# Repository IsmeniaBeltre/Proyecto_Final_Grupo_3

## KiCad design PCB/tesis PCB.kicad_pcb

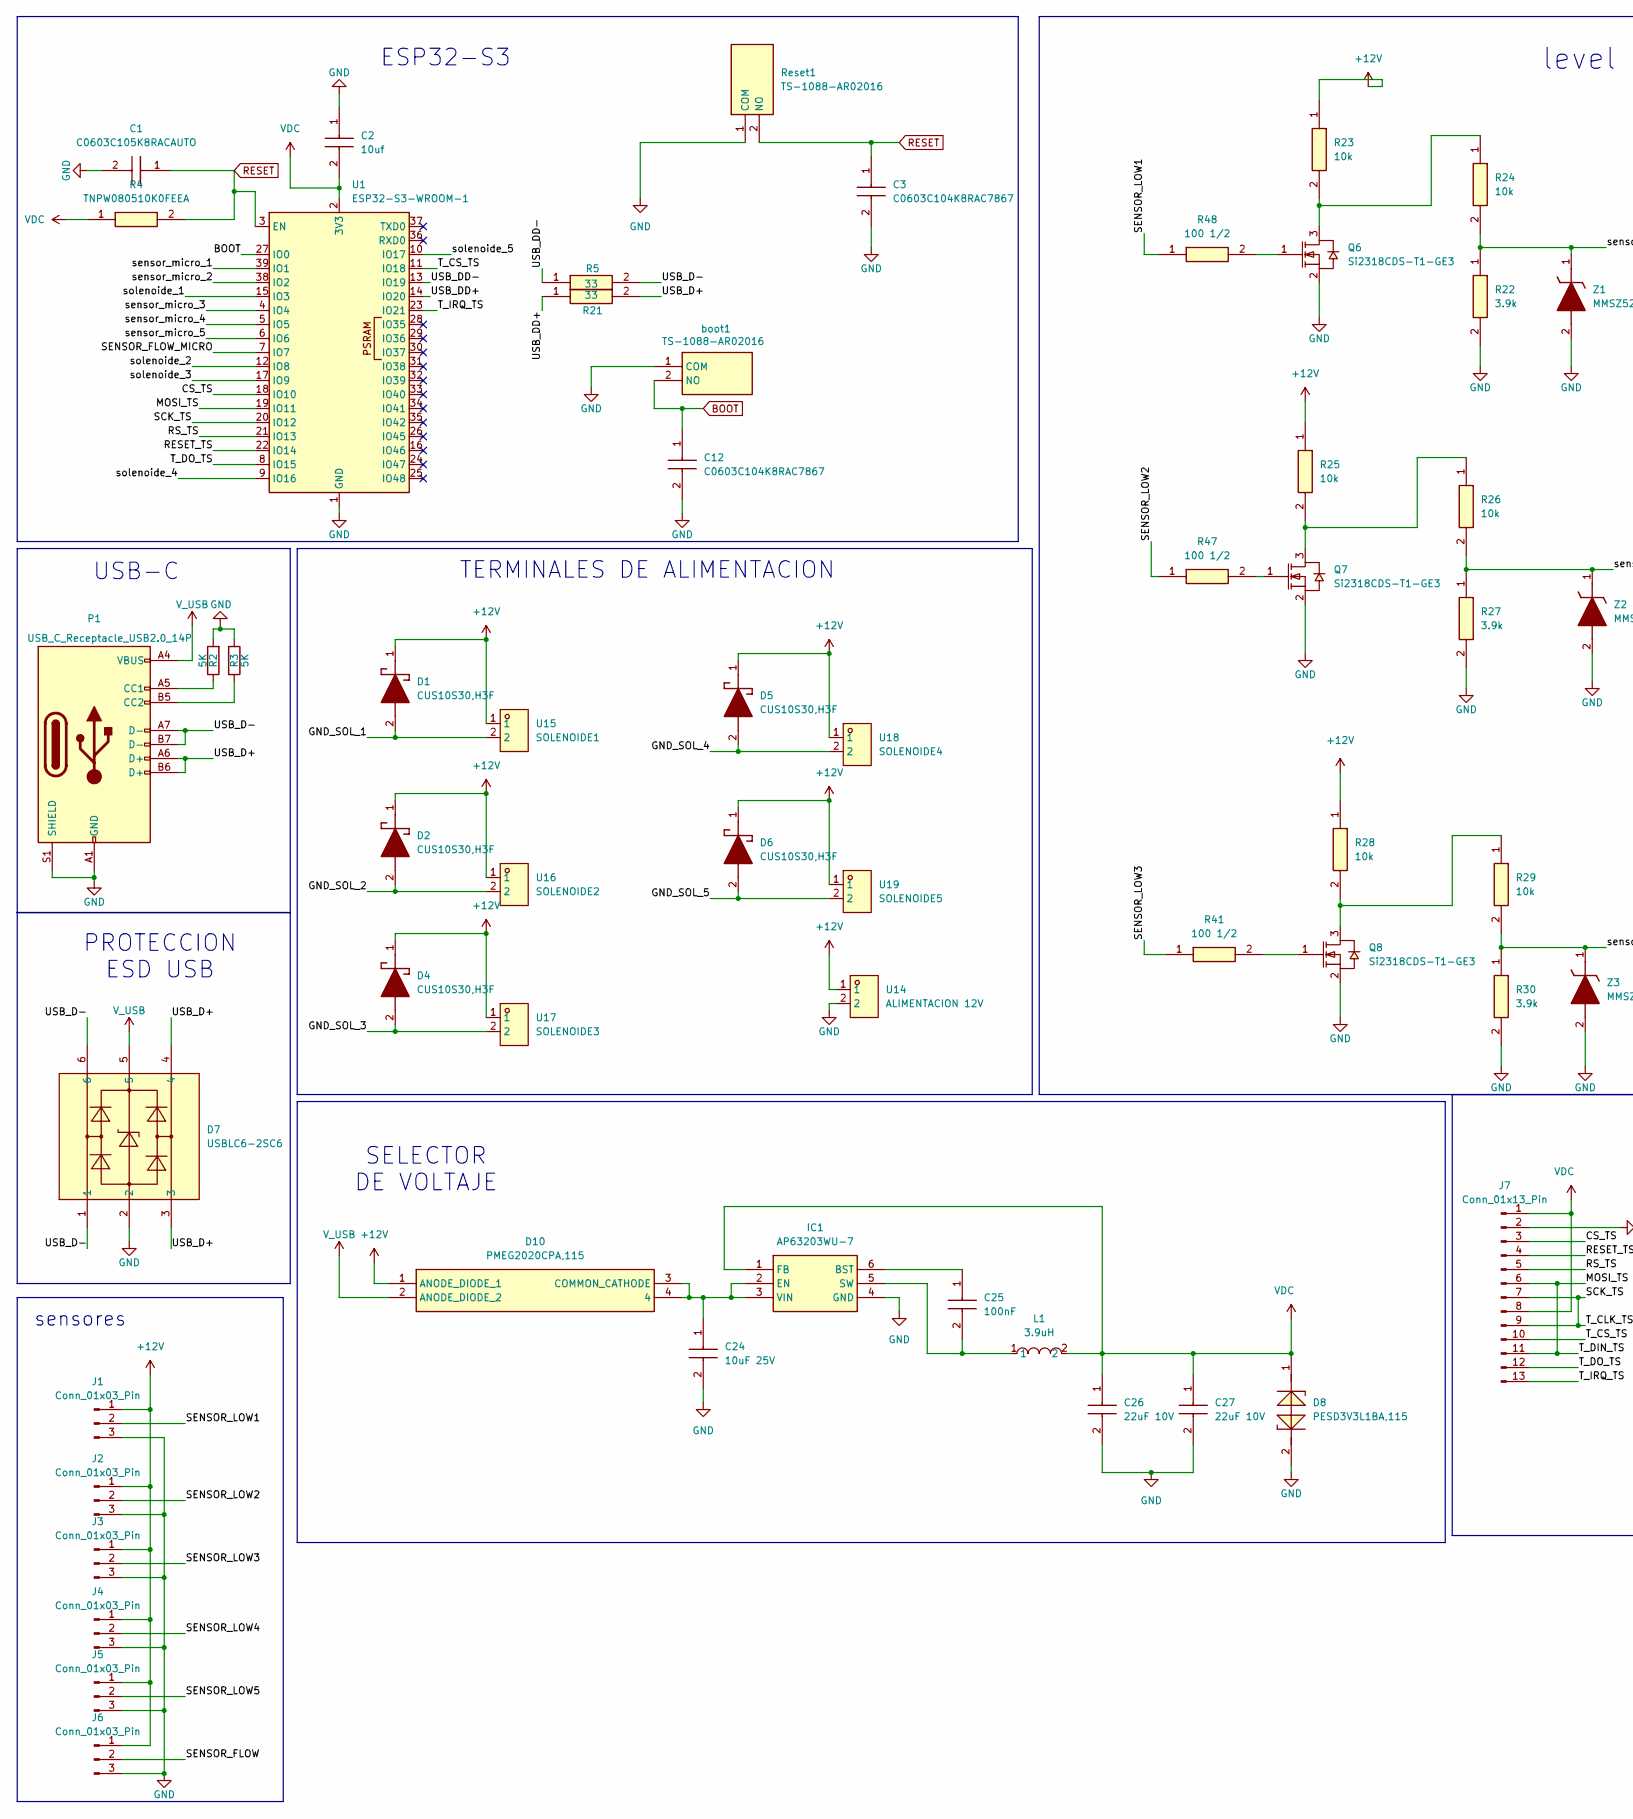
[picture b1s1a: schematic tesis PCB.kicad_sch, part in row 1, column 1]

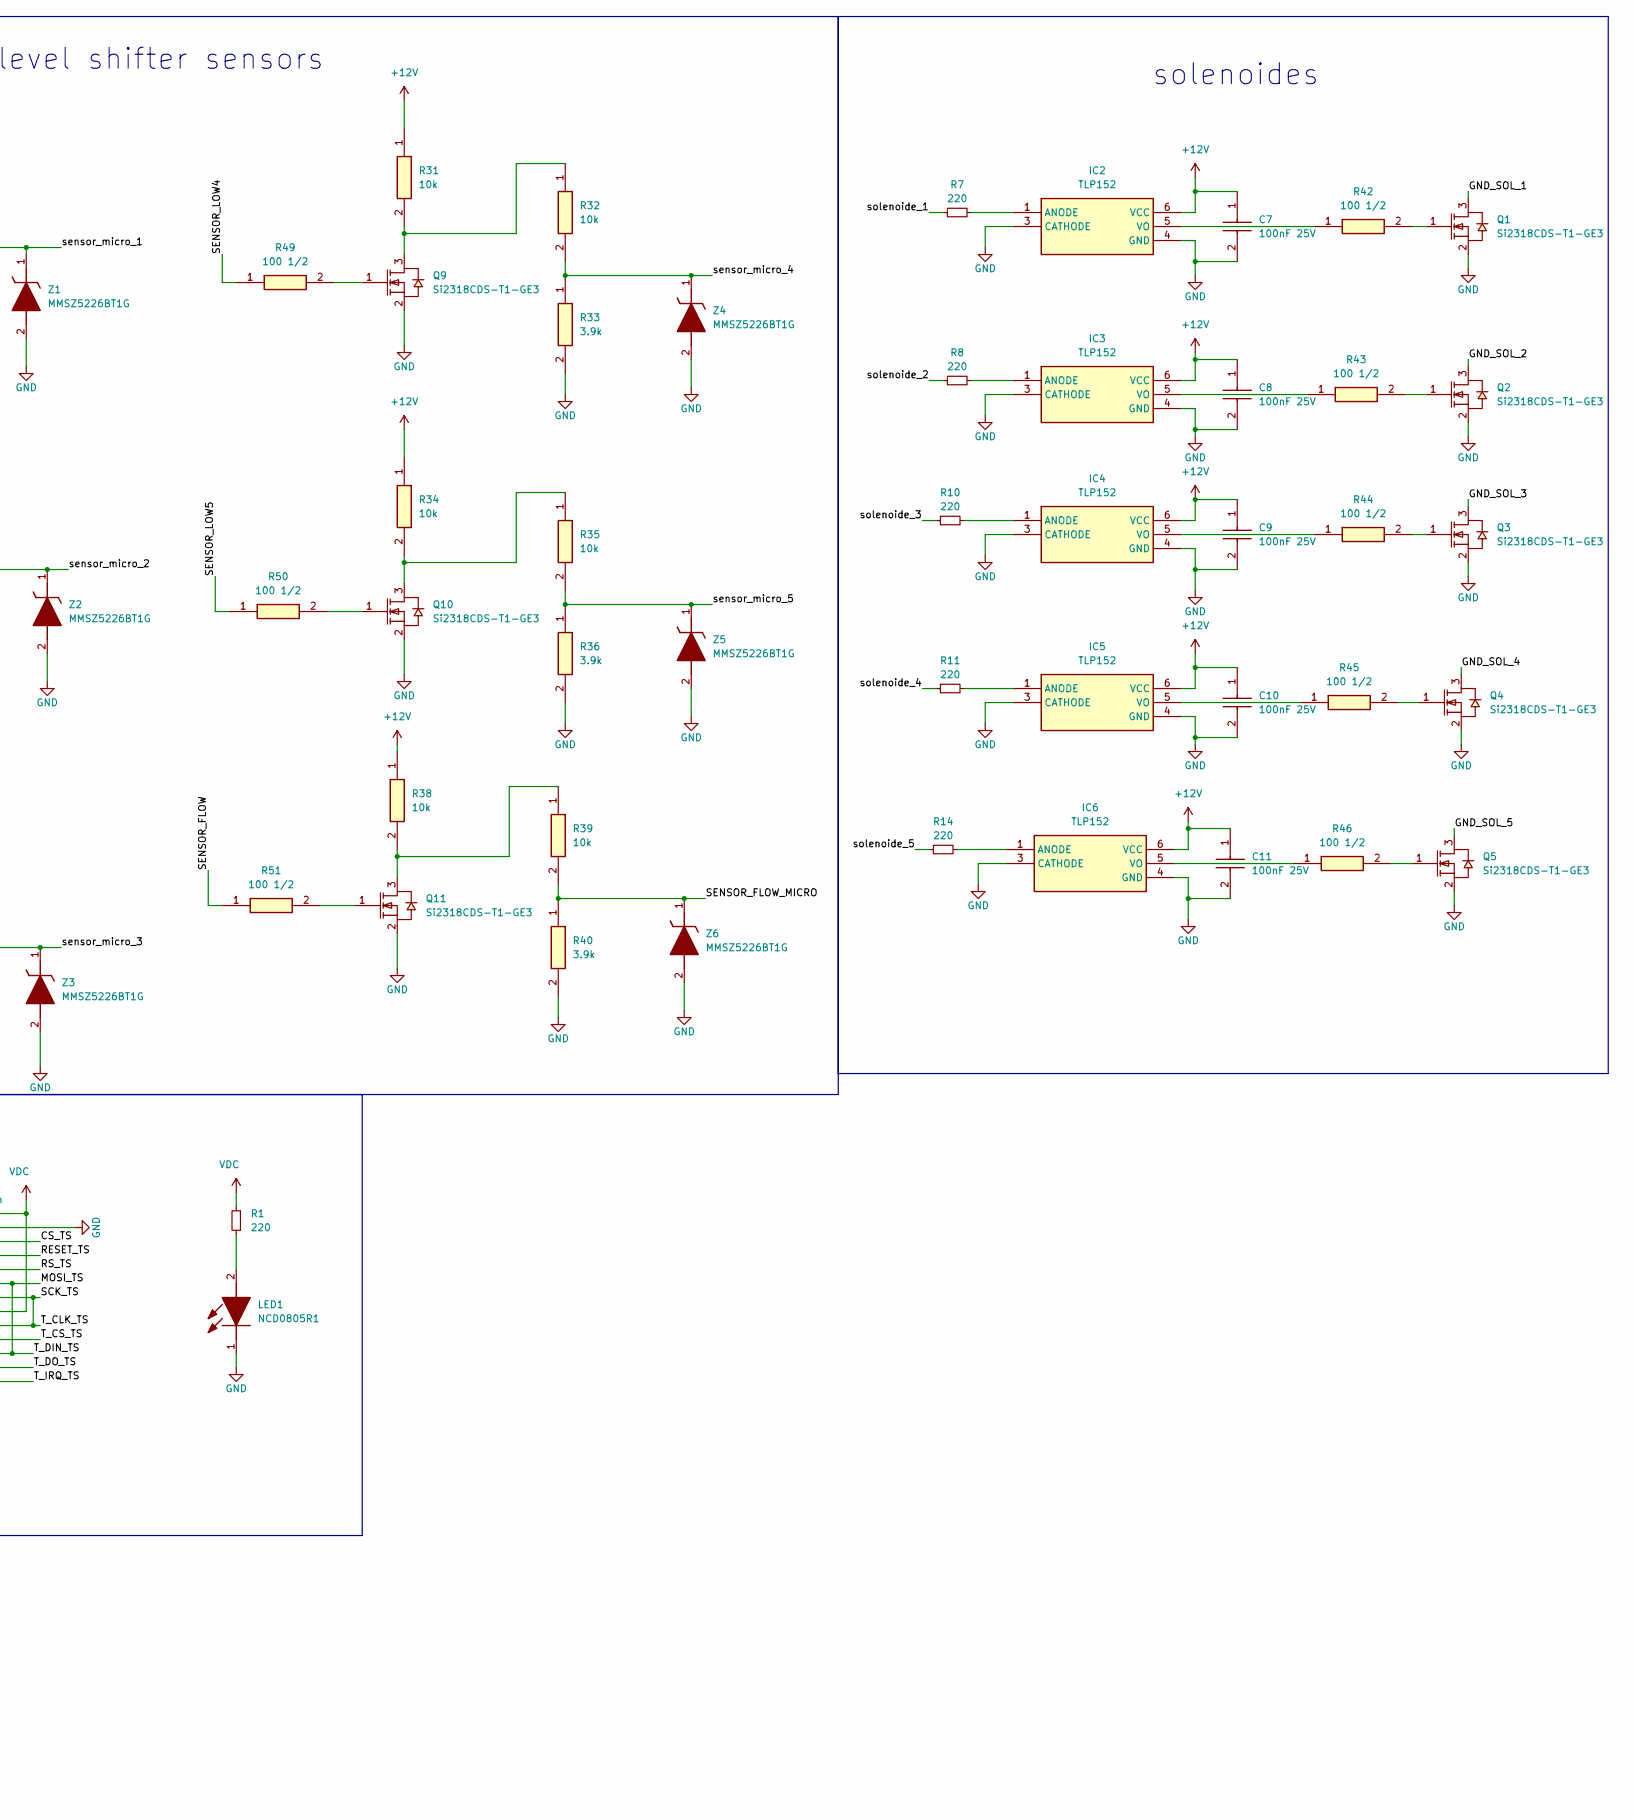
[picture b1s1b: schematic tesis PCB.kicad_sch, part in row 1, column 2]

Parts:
C1: C0603C105K8RACAUTO; C0603; Manufacturer_Part_Number C0603C105K8RACAUTO; Mouser Part Number 80-C0603C105K8RAUTO
C2: 10uf; C0805; Manufacturer_Part_Number C0805C106M8RACAUTO; Mouser Part Number 80-C0805C106M8RAUTO
C3, C12: C0603C104K8RAC7867; CAPC1608X87N; Manufacturer_Part_Number C0603C104K8RAC7867; Mouser Part Number N/A
C7, C8, C9, C10, C11: 100nF 25V; CAPC1608X90N; Manufacturer_Part_Number CL10B104KA8NNNC; Mouser Part Number 187-CL10B104KA8NNNC
C24: 10uF 25V; CAPC2012X145N; Manufacturer_Part_Number CL21B106KAYQNNE; Mouser Part Number 187-CL21B106KAYQNNE
C25: 100nF; CAPC1608X87N; Manufacturer_Part_Number C0603C104K8RAC7867; Mouser Part Number N/A
C26, C27: 22uF 10V; GRM21BR60J226ME39L; Manufacturer_Part_Number GRM21BZ71A226ME15L; Mouser Part Number 81-GRM21BZ71A226ME5L
D1, D2, D4, D5, D6: CUS10S30,H3F; 1SS357TPH3F; Manufacturer_Part_Number CUS10S30,H3F; Mouser Part Number 757-CUS10S30H3F
D7: USBLC6-2SC6; SOT95P280X145-6N; LCSC Part C7519
D8: PESD3V3L1BA,115; SOD2512X110N; LCSC Part C51450
D10: PMEG2020CPA,115; PMEG2020CPA115; Manufacturer_Part_Number PMEG2020CPA,115; Mouser Part Number 771-PMEG2020CPA115
IC1: AP63203WU-7; AP63203WU7; Mouser Part Number 621-AP63203WU-7
IC2, IC3, IC4, IC5, IC6: TLP152; 11-4L1S_5-PIN-SOIC_; Manufacturer_Part_Number TLP152; Mouser Part Number N/A
J1, J2, J3, J4, J5, J6: Conn_01x03_Pin; HDRV3W64P0X254_1X3_762X250X890P
J7: Conn_01x13_Pin; HDR-TH_13P-P2.54-V-M; lcsc part C5242246
L1: 3.9uH; IND-SMD_TNR4030S-3R9MTF; LCSC Part C42380168
LED1: NCD0805R1; LEDC2012X120N; Manufacturer_Part_Number NCD0805R1
P1: USB_C_Receptacle_USB2.0_14P; USB_C_Receptacle_GCT_USB4105-xx-A_16P_TopMnt_Horizontal
Q1, Q2, Q3, Q4, Q5, Q6, Q7, Q8, Q9, Q10, Q11: Si2318CDS-T1-GE3; SOT95P237X112-3N; LCSC Part C14498
R1, R7, R8, R10, R11, R14: 220; RESC1609X55N
R2, R3: 5K; RESC1608X55N; LCSC C862232
R4: TNPW080510K0FEEA; RESC2012X55N; Manufacturer_Part_Number TNPW080510K0FEEA; Mouser Part Number 71-TNPW080510K0FEEA
R5, R21: 33; RESC1608X55N; Manufacturer_Part_Number RC0603FR-0733RL; Mouser Part Number 603-RC0603FR-0733RL
R22, R27, R30, R33, R36, R40: 3.9k; RESC1608X55N; Manufacturer_Part_Number RC0603FR-073K9L; Mouser Part Number 603-RC0603FR-073K9L
R23, R24, R25, R26, R28, R29, R31, R32, R34, R35, R38, R39: 10k; RESC2012X55N; Manufacturer_Part_Number TNPW080510K0FEEA; Mouser Part Number 71-TNPW080510K0FEEA
R41, R42, R43, R44, R45, R46, R47, R48, R49, R50, R51: 100 1/2; RESC3126X65N; Manufacturer_Part_Number RC1210FR-07100RL
Reset1: TS-1088-AR02016; TS1088AR02016; Manufacturer_Part_Number TS-1088-AR02016
U1: ESP32-S3-WROOM-1
U14: ALIMENTACION 12V; KF1282542P; LCSC Part C474920
U15: SOLENOIDE1; KF1282542P; LCSC Part C474920
U16: SOLENOIDE2; KF1282542P; LCSC Part C474920
U17: SOLENOIDE3; KF1282542P; LCSC Part C474920
U18: SOLENOIDE4; KF1282542P; LCSC Part C474920
U19: SOLENOIDE5; KF1282542P; LCSC Part C474920
Z1, Z2, Z3, Z4, Z5, Z6: MMSZ5226BT1G; SOD3716X135N; Manufacturer_Part_Number MMSZ5226BT1G; Mouser Part Number 863-MMSZ5226BT1G
boot1: TS-1088-AR02016; TS1088AR02016; Manufacturer_Part_Number TS-1088-AR02016

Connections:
+12V: C7.1, C8.1, C9.1, C10.1, C11.1, D1.1 (K), D2.1 (K), D4.1 (K), D5.1 (K), D6.1 (K), D10.1 (ANODE_DIODE_1), IC2.6 (VCC), IC3.6 (VCC), IC4.6 (VCC), IC5.6 (VCC), IC6.6 (VCC), J1.1, J2.1, J3.1, J4.1, J5.1, J6.1, R23.1, R25.1, R28.1, R31.1, R34.1, R38.1, U14.1, U15.1, U16.1, U17.1, U18.1, U19.1
/CS_TS: J7.3, U1.18 (IO10)
/GND_SOL_1: D1.2 (A), Q1.3, U15.2
/GND_SOL_2: D2.2 (A), Q2.3, U16.2
/GND_SOL_3: D4.2 (A), Q3.3, U17.2
/GND_SOL_4: D5.2 (A), Q4.3, U18.2
/GND_SOL_5: D6.2 (A), Q5.3, U19.2
/MOSI_TS: J7.6, J7.11, U1.19 (IO11)
/RESET_TS: J7.4, U1.22 (IO14)
/RS_TS: J7.5, U1.21 (IO13)
/SCK_TS: J7.7, J7.9, U1.20 (IO12)
/SENSOR_FLOW: J6.2, R51.1
/SENSOR_FLOW_MICRO: R39.2, R40.1, U1.7 (IO7), Z6.1 (K)
/SENSOR_LOW1: J1.2, R48.1
/SENSOR_LOW2: J2.2, R47.1
/SENSOR_LOW3: J3.2, R41.1
/SENSOR_LOW4: J4.2, R49.1
/SENSOR_LOW5: J5.2, R50.1
/T_CS_TS: J7.10, U1.11 (IO18)
/T_DO_TS: J7.12, U1.8 (IO15)
/T_IRQ_TS: J7.13, U1.23 (IO21)
/USB_D+: D7.3, D7.4, P1.A6 (D+), P1.B6 (D+), R21.2
/USB_D-: D7.1, D7.6, P1.A7 (D-), P1.B7 (D-), R5.2
/USB_DD+: R21.1, U1.14 (IO20)
/USB_DD-: R5.1, U1.13 (IO19)
/sensor_micro_1: R22.1, R24.2, U1.39 (IO1), Z1.1 (K)
/sensor_micro_2: R26.2, R27.1, U1.38 (IO2), Z2.1 (K)
/sensor_micro_3: R29.2, R30.1, U1.4 (IO4), Z3.1 (K)
/sensor_micro_4: R32.2, R33.1, U1.5 (IO5), Z4.1 (K)
/sensor_micro_5: R35.2, R36.1, U1.6 (IO6), Z5.1 (K)
/solenoide_1: R7.1, U1.15 (IO3)
/solenoide_2: R8.1, U1.12 (IO8)
/solenoide_3: R10.1, U1.17 (IO9)
/solenoide_4: R11.1, U1.9 (IO16)
/solenoide_5: R14.1, U1.10 (IO17)
BOOT: C12.1, U1.27 (IO0), boot1.2 (NO)
GND: C1.2, C2.1, C3.2, C7.2, C8.2, C9.2, C10.2, C11.2, C12.2, C24.2, C26.2, C27.2, D7.2, D8.2, IC1.4 (GND), IC2.3 (CATHODE), IC2.4 (GND), IC3.3 (CATHODE), IC3.4 (GND), IC4.3 (CATHODE), IC4.4 (GND), IC5.3 (CATHODE), IC5.4 (GND), IC6.3 (CATHODE), IC6.4 (GND), J1.3, J2.3, J3.3, J4.3, J5.3, J6.3, J7.2, LED1.1 (K), P1.A1 (GND), P1.A12 (GND), P1.B1 (GND), P1.B12 (GND), P1.S1 (SHIELD), Q1.2, Q2.2, Q3.2, Q4.2, Q5.2, Q6.2, Q7.2, Q8.2, Q9.2, Q10.2, Q11.2, R2.2, R3.1, R22.2, R27.2, R30.2, R33.2, R36.2, R40.2, Reset1.1 (COM), U1.1 (GND), U1.40 (GND), U1.41 (GND), U14.2, Z1.2 (A), Z2.2 (A), Z3.2 (A), Z4.2 (A), Z5.2 (A), Z6.2 (A), boot1.1 (COM)
unnamed: C24.1, D10.3 (COMMON_CATHODE), D10.4, IC1.2 (EN), IC1.3 (VIN)
unnamed: C25.1, IC1.6 (BST)
unnamed: C25.2, IC1.5 (SW), L1.1
unnamed: IC2.1 (ANODE), R7.2
unnamed: IC2.5 (VO), R42.1
unnamed: IC3.1 (ANODE), R8.2
unnamed: IC3.5 (VO), R43.1
unnamed: IC4.1 (ANODE), R10.2
unnamed: IC4.5 (VO), R44.1
unnamed: IC5.1 (ANODE), R11.2
unnamed: IC5.5 (VO), R45.1
unnamed: IC6.1 (ANODE), R14.2
unnamed: IC6.5 (VO), R46.1
unnamed: LED1.2 (A), R1.1
unnamed: P1.A5 (CC1), R2.1
unnamed: P1.B5 (CC2), R3.2
unnamed: Q1.1, R42.2
unnamed: Q2.1, R43.2
unnamed: Q3.1, R44.2
unnamed: Q4.1, R45.2
unnamed: Q5.1, R46.2
unnamed: Q6.1, R48.2
unnamed: Q6.3, R23.2, R24.1
unnamed: Q7.1, R47.2
unnamed: Q7.3, R25.2, R26.1
unnamed: Q8.1, R41.2
unnamed: Q8.3, R28.2, R29.1
unnamed: Q9.1, R49.2
unnamed: Q9.3, R31.2, R32.1
unnamed: Q10.1, R50.2
unnamed: Q10.3, R34.2, R35.1
unnamed: Q11.1, R51.2
unnamed: Q11.3, R38.2, R39.1
RESET: C1.1, C3.1, R4.2, Reset1.2 (NO), U1.3 (EN)
VDC: C2.2, C26.1, C27.1, D8.1, IC1.1 (FB), J7.1, J7.8, L1.2, R1.2, R4.1, U1.2 (3V3)
V_USB: D7.5, D10.2 (ANODE_DIODE_2), P1.A4 (VBUS), P1.A9 (VBUS), P1.B4 (VBUS), P1.B9 (VBUS)

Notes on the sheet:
SELECTOR DE VOLTAJE
solenoides
USB-C
sensores
PROTECCION ESD USB
TERMINALES DE ALIMENTACION
ESP32-S3
level shifter sensors

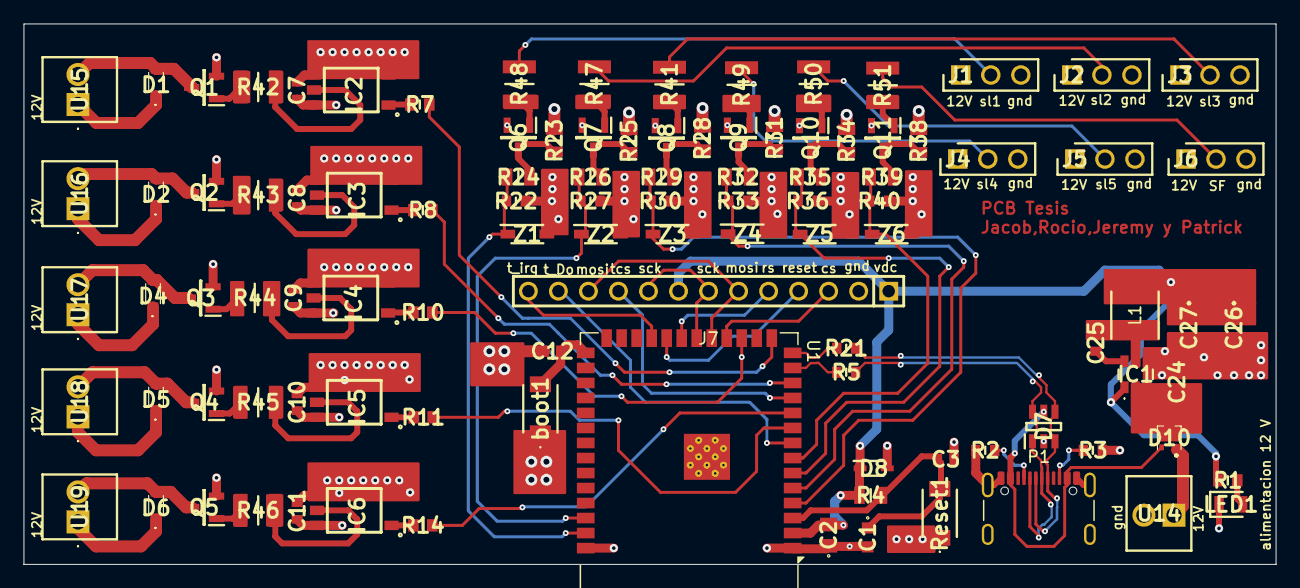
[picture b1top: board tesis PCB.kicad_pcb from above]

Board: 4 copper layers, 105.9 x 45.7 mm, 103 parts (0 on the bottom side), 73 nets.
